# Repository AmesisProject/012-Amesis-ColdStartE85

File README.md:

# 012-Amesis-ColdStartE85
 Version 1.00 du document ( Vous pouvez me commander des PCB, faites vos demandes à amesisproject@gmail.com)
 
012-Amesis-ColdStartE85
Module d’aide au démarrage à froid pour les moteurs utilisant le carburant Superéthanol E85 dont la cartographie de démarrage à froid n’a pas été réglé.
Les conventions des moteurs à l’éthanol ont généralement un souci mangeur, c’est le ColdStart.

En effet, l’éthanol à son point éclaire à 7 degrés contre -40 pour le super sans plomb. Ce qui entraine donc un démarrage plus difficile voire impossible. 

Module mise au point pour le moteur de Golf IV 1.6L 16v essence passé à l’E85. Equipé du calculateur Magneti Marelli 4MV, mais peut fonctionner sur d’autre model tel quel. A vous d’analyser vos capteurs et signaux pour modifier le code.   

## I Avertissement
 
Ce module n’est nullement homologué, il sera donc fourni à but de test et non à une utilisation sur voie public.
 
Ce module modifiant le signal d’un capteur d’origine, les possibilités d’endommagement de l’ECU ou du moteur reste donc une éventualité. Vous restez seul responsable de l’utilisation de ce module. 
 
Ce module agissant sur des capteurs d’origine du véhicule pourrait entrainer des codes défaut moteur intermittent ou permanant, dans ce cas il est déconseillé de l’utiliser. 
 
Le module a pour but de décaler la plage de temperature du liquide de refroidissement ce qui correspond à des valeurs d’injection et d’allumage plus importante dans les cartographies moteur. Ces cartographies sont généralement très difficiles à modifier car le mappeur doit attendre une température adéquate pour son réglage car le moindre démarrage moteur réchauffe instantanément et rapidement le moteur du fait de la compression de l’air et de la combustion. Il faut attendre plusieurs heures afin de retenter un nouveau réglage, ce qui est parfois laborieux pour les mappeurs. 

C’est donc pour cela que ce module a été créer. 
 
De plus les cartographies de démarrage à froid « cold star » sur les calculateurs ECU Magneti Marelli 4MV sont encore un mystère dans notre communauté.

Cette documentation consterne le module en version matériel 
HW : v0.01dev et logiciel
SW Firmware : v1.031 Béta

Ce module est en version Beta, il sera donc apprécié tout retour d’information positif ou négatif à son sujet pour des nouvelle amélioration matériel et logiciel. 
Vous pouvez nous faire une proposition de modification de cade pas « Pull Requests » de GitHub ou de nous informer sur n’importe quel sujet, problème, bug et améliorations à venir, dans la partie « Issues ». Du repos GitHub du projet « 012-Amesis-ColdStartE85 »
https://github.com/AmesisProject/012-Amesis-ColdStartE85

## II Schéma de câblage
 
Type de branchement possible
Chercher et trouver la sonde de temperature du liquide de refroidissement.
 
La sonde G2 chez le groupe VAG informe la temperature au compteur.
 
La sonde G62 chez le groupe VAG informe la temperature au calculateur moteur (ECU).
 
Pour ce module c’est la sonde de temperature moteur qui nous intéresse. 
 
Ceci a été tester sur une Golf IV 1.6L 16s équipé d’un ECU Magneti Marelli. Ce qui est impotent c’est que la sonde de température du véhicule soit de type NTC c’est à dire que plus elle se réchauffe plus sa résistance réduit (plus elle se rapproche de 0.00 Ohm).
 
Le module doit être raccordé à un plus après contacte et protégé par un fusible 1A (à vérifier suivant la consommation de courant du module) :
 
1)	Sonde à 2 fils (nommer G62 chez le groupe VAG)

2)	Sonde à 4 fils (nommer G2 et G62 chez lez groupe VAG, les deux sondes sont dans le même boitier)

## III Options du module
 
  Le module est équipé des trois Pins accessible, se qui permet de sélectionner les options.
1)	 Option 1
Aucun jumpeur d’installer :
  
Dans ce cas, le module et inactif, une fois le contacte mis, il lesse passe le signal d’origine de la sonde de temperature d’origine.

2)	Option 2
Ponter le jumpeur entre le pin 1 et le pin 2 :
   
Dans ce cas, le module et activer. Il modifie le signal d’origine pour augmenter légèrement l’enrichissement et/ou l’allumage au démarrage.

3)	Option 3
Ponter le jumpeur entre le pin 2 et le pin 3 :
   
Dans ce cas, le module et activer. Il modifie le signal d’origine pour augmenter moyennement l’enrichissement et/ou l’allumage au démarrage.

4)	Option 4
Ponter le jumpeur entre le pin 1, le pin 2 et le pin 3 :
   
Dans ce cas, le module et activer. Il modifie le signal d’origine pour augmenter fortement l’enrichissement et/ou l’allumage au démarrage.
IV Fonctionnement
Une fois le contacte mis, 2 solutions :

1)	Solution 1
Le module n’a pas l’option sonde de temperature additionnelle, dans ce cas, suivant l’option engagée, le module sera actif pendant environ 1 min en modifiant le signe d’origine de manière dégressif jusqu’à atteindre la valeur d’origine après environ 1 min. Passé ce délai, le module passe en mode inactif pour laisser l’ECU d’origine faire son travail normalement.
Sans l’option la sonde de temperature additionnelle le module sera actif à chaque mis sous contacte du véhicule

2)	Solution 2
Le module est équipé de la sonde de temperature additionnelle. Celle-ci devra être placer à proximité d’une source de chaleur venant du moteur, par exemple une durite de liquide de refroidissement du circuit cour. 
La sonde de temperature additionnelle ne doit pas être installer en contacte direct avec des organes du moteur pouvant dépasser une centaine de degré sous peine de risque de détérioration de la sonde voir pire risque d’incendies. 

Suivant l’option engagé, si le module a bien la sonde de temperature additionnelle, il sera en mesure de comprendre s’il est nécessaire d’activer l’enrichissement à froid suivant la temperature à la sonde de temperature additionnelle.

Pour la version du HW Firmware v1.031 béta, le seuil de d’déclanchement est approximativement en dessous des 30° de la sonde de temperature additionnelle. Si cette valeur et dépassé, alors le module passe en mode inactif car au-delà de cette temperature, le mode enrichissement à froid est inutile.
Cette valeur pourra être ajusté à la demande si besoin par une mise à jour FW.

## V Communication

Le module est pourvu d’un port USB. Il permet de communiquer avec un ordinateur pour contrôler la version du SW HW et les valeurs retournées du module car le décompte du « cold start » et option engagé.

Pour afficher ces valeurs, vous devez vous munir d’un ordinateur Windows, Mac ou Linux avec le logiciel gratuit IDE Arduino d’installer.

Dans le logiciel vous devrez choisir l‘adresse du port USB utilisé par ex :

-Sur Windows Onglet « Outils » -> « Port » -> « Port Com 4 » 

-Puis ouvrir la console de debug avec l’icône loupe en haut à droite de la fenetre du logiciel Arduino.

-Régler la vitesse sur 115200 Baud

Et les valeurs commenceront à défiler dans la fenetre.

ATTENTION Ce logiciel peut écraser les données du microcontrôleur si vous téléverser un nouveau code. 

Il faudra obligatoirement téléverser le code d’origine pour que le module refonctionne normalement.

#Don 

J'ai travaillé ennormement sur ce projet entre le code, la fabrication du PCB et les testes sur la Golf IV 1.6L essese de Mich. Me faire un don me motive pour continuer de mettre en ligne des projets gratuitement.

https://www.paypal.com/donate/?cmd=_s-xclick&hosted_button_id=R9SMSS8L6FZB2&source=url&ssrt=1681586896608

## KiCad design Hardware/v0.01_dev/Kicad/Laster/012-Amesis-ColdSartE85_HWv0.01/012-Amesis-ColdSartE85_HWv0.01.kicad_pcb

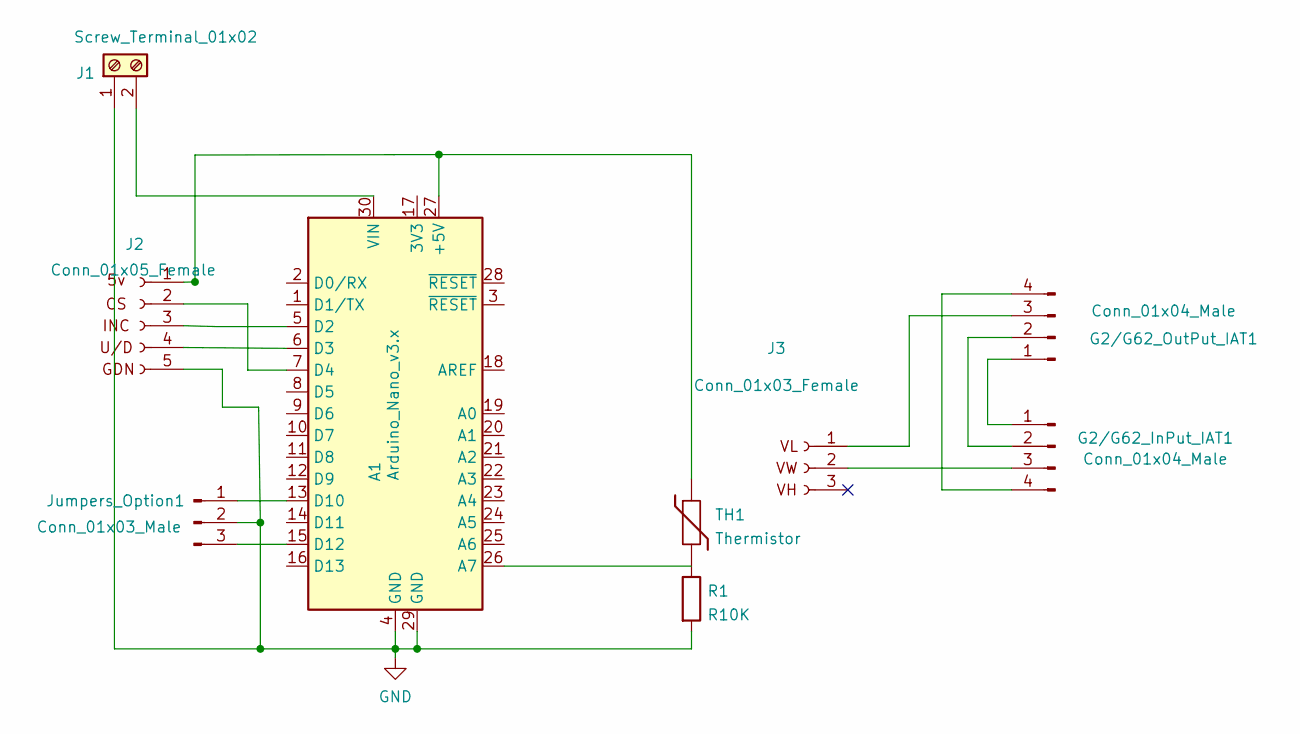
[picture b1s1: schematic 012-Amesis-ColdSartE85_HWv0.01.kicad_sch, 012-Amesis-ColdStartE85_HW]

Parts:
A1: Arduino_Nano_v3.x; Arduino_Nano
G2/G62_InPut_IAT1, G2/G62_OutPut_IAT1: Conn_01x04_Male; TerminalBlock_bornier-4_P5.08mm
J1: Screw_Terminal_01x02; TerminalBlock_bornier-2_P5.08mm
J2: Conn_01x05_Female; PinSocket_1x05_P2.54mm_Vertical
J3: Conn_01x03_Female; PinSocket_1x03_P2.54mm_Vertical
Jumpers_Option1: Conn_01x03_Male; PinHeader_1x03_P2.54mm_Vertical
R1: R10K; R_Axial_DIN0204_L3.6mm_D1.6mm_P5.08mm_Horizontal
TH1: Thermistor; PinHeader_1x02_P2.54mm_Vertical

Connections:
GND: A1.4 (GND), A1.29 (GND), J1.1, J2.5, Jumpers_Option1.2, R1.2
unnamed: A1.5 (D2), J2.3
unnamed: A1.6 (D3), J2.4
unnamed: A1.7 (D4), J2.2
unnamed: A1.13 (D10), Jumpers_Option1.1
unnamed: A1.15 (D12), Jumpers_Option1.3
unnamed: A1.26 (A7), R1.1, TH1.2
unnamed: A1.27 (+5V), J2.1, TH1.1
unnamed: A1.30 (VIN), J1.2
unnamed: G2/G62_InPut_IAT1.1, G2/G62_OutPut_IAT1.1
unnamed: G2/G62_InPut_IAT1.2, G2/G62_OutPut_IAT1.2
unnamed: G2/G62_InPut_IAT1.3, J3.2
unnamed: G2/G62_InPut_IAT1.4, G2/G62_OutPut_IAT1.4
unnamed: G2/G62_OutPut_IAT1.3, J3.1

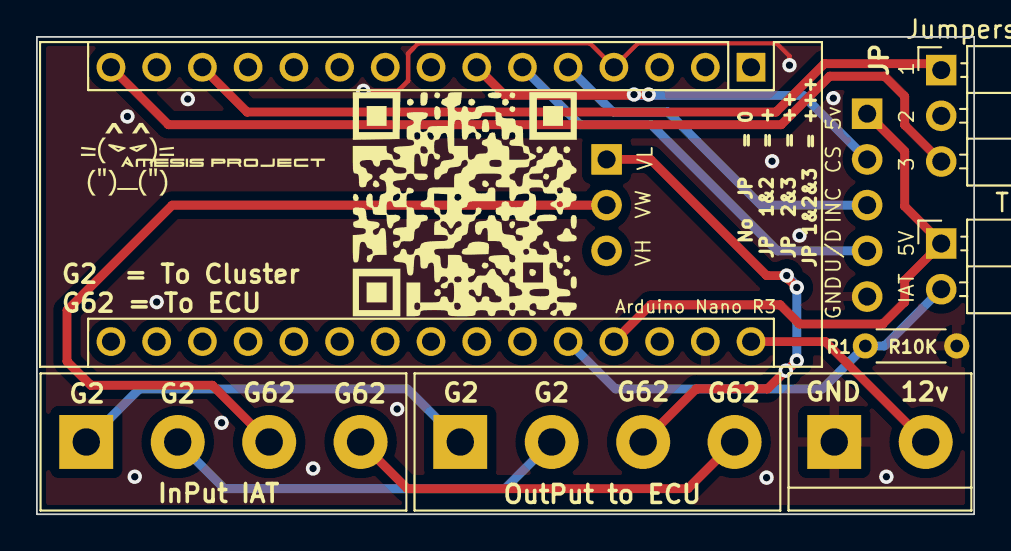
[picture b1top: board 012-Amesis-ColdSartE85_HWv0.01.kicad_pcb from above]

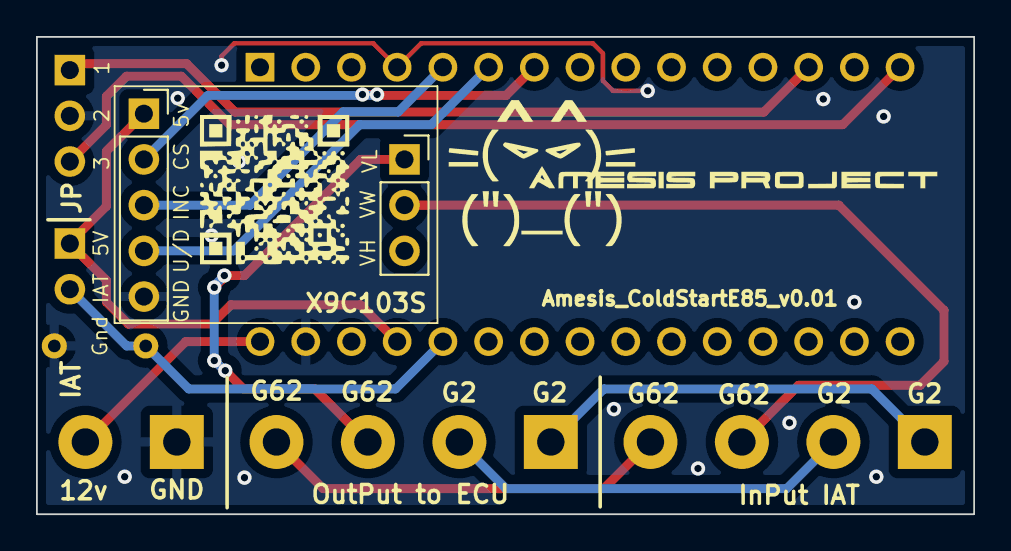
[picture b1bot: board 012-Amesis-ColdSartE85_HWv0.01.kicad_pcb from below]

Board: 2 copper layers, 52.1 x 26.5 mm, 13 parts (4 on the bottom side), 14 nets.

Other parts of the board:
 : LOGO; 15x15 KiCad QR Code La Boutique Amesis Project
 #2: LOGO; AmesisProject Logo 15mm
 #3: LOGO; AmesisProject Logo 30mm
 #4: LOGO; 10x10 KiCad QR Code La Boutique Amesis Project

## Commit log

2022-08-25 Mise place du projet
    Creation des 1er fichier
2022-08-25 Update 012-Amesis-ColdStartE85.ino
    Debut de creation du fichier
2022-08-25 creation de la vertion v0.2
    Création d'un v0.02
2022-08-25 Create SharedScreenshot.jpg
    schemat de la sonde de temps Liqui de refroidissement
2022-08-25 Ajout schémas
2022-08-25 Create sonde t.jpg
    mise en ligne de la sonde data
2022-08-25 Ajout photos sonde ldr
2022-08-25 supretion
    supre
2022-08-25 Create data sonde ot.jpg
    data
2022-08-25 Map Linea ols + Alglo Du projet
2022-08-26 ajout graphique fonctionnement sonde
2022-08-28 Creation du code arduino de teste
2022-08-29 Ajouts images + réorganisation
2022-09-09 impor de la savegarde
2022-09-15 kicad en cour
2022-09-20 Création du PCB
    En cour. le controleur de rootage affiche quelques erreurs
2022-09-28 PCB prèsque fini (qr code a modifier
2022-09-28 Debut du code de test du module potar numerique
2022-09-28 Code Arduino Module v0.01 Alfa ok
2022-09-28 en cour v0.02
2022-09-29 maj
    pcb fini
    visu fini
    iBom fini HWv.0.01
2022-09-29 maj pcb
2022-10-01 maj pcb et code arduino avec jp et sonde iat
2022-10-02 ajouts datasheet & images sonde température
2022-10-03 Update 012-Amesis-ColdStartE85.ino
    pofinage du code
2022-10-03 code v0.02
    termista
2022-10-04 test v0.03
2022-10-09 Update 012-Amesis-ColdStartE85.ino
    finalisation du code, reste a faire la routine en cas de DTC = 1
2022-10-09 Update 012-Amesis-ColdStartE85.ino
    correction d'un int en long pour voir plus de temps
2022-10-09 Création de la version V1.00Béta
    Près a faire feu pour des teste réel
2022-10-29 xloader
2022-10-29 FirmWare v1.03 OK avec HW v0.01Dev
    Création d'une version de developeur et une vertion utilisateur pour le client. La vertion utilisateur et la meme que la dev mais sans l'info sur la console pour la valeur de la sonde de temperature.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
2022-10-29 Archivage v1.03 beta
2022-10-31 photo
2022-11-02 Création v1.031 SW
    Supression du delay dans le setup
    commande du lap a 0 ohm plus haut dans le setup
2022-11-03 correction sonde température additionnel
2022-11-04 Manuel d'utilisation
2022-11-04 Mia du manuel
